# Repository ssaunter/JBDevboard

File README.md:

# JBDevboard
A custom RP2040 dev board utilizing a NCP1117 LDO. This project is a modified version of the RP2040 devboard project by [Kai Pereira](https://github.com/KaiPereira/build-a-devboard), which has served as a great resource for learning about devboard production. This board is essentially a clone of a Raspberry Pi RP2040 board.

Here is a look at the current build:

The large IC near the back of the board, labeled U2, is the NCP1117. It is capable of providing an output current of 1.0 A, which is an upgrade from the LDOs in the tutorial, which has a max output current of 250 mA.

Here's the schematic:
---

And here's what the trace layers look like:
---

---
### Bill of Materials
---

| Part | Quantity | Price Per | Link | 
| :--- | :---: | :---: | :--- |
| **RP2040** | 1 | $0.70 | [DigiKey](https://www.digikey.com/short/ndb2782v) |
| **NCP1117** | 1 | $0.37 | [DigiKey](https://www.digikey.com/short/5j4t47bt) |
| **USB-C Recepticle** | 1 | $0.47 | [DigiKey](https://www.digikey.com/short/z2dbcnt0) |
| **W25Q128JVEIM TR** | 1 | $2.31 | [DigiKey](https://www.digikey.com/short/mfqznn09) |
| **12 Mhz Xtal Osc** | 1 | $1.35 | [DigiKey](https://www.digikey.com/short/h02qvddd) |
| **1x20 Header** | 2 | $0.50 |[DigiKey](https://www.digikey.com/short/dqz7fj2b) |
| **1x3 Header** | 1 | $0.17 | [DigiKey](https://www.digikey.com/short/td5n0hbf) |
| **5.1k R 0402** | 2 | $0.10 |[DigiKey](https://www.digikey.com/short/c9z4njr9) |
| **27.4 R 0402** | 2 | $0.10 |[DigiKey](https://www.digikey.com/short/pqdzv9nf) |
| **1k R 0402** | 2 | $0.10 | [DigiKey](https://www.digikey.com/short/ptpr3b5v) |
| **10k R 0402** | 1 | $0.10 |[DigiKey](https://www.digikey.com/short/1bqf9rrt) |
| **0.1uF C 0402** | 11 | $0.03 |[DigiKey](https://www.digikey.com/short/prnwd7b4) |
| **1uF C 0402** | 1 | $0.08 | [DigiKey](https://www.digikey.com/short/bh2hq3n5) |
| **33pF C 0402** | 2 | $0.10 |[DigiKey](https://www.digikey.com/short/87qt971h) |
| **10uF C 0603** | 2 | $0.47 |[DigiKey](https://www.digikey.com/short/22nm5zq0) |
| **Push Button** | 1 | $0.41 | [DigiKey](https://www.digikey.com/short/8bz14998) |
| **PCB** | 1 | $2.10 | [JCLPCB](https://jlcpcb.com/) |
| **PCB Stencil** | 1 | $7.11 | [JCLPCB](https://jlcpcb.com/) |
| **JLCPCB Tax + Shipping** |  | ~$20.31 | |
| **DigiKey Tax + Shipping** |  | ~$8.56 | 
| **TOTAL** |  | $46.12 |

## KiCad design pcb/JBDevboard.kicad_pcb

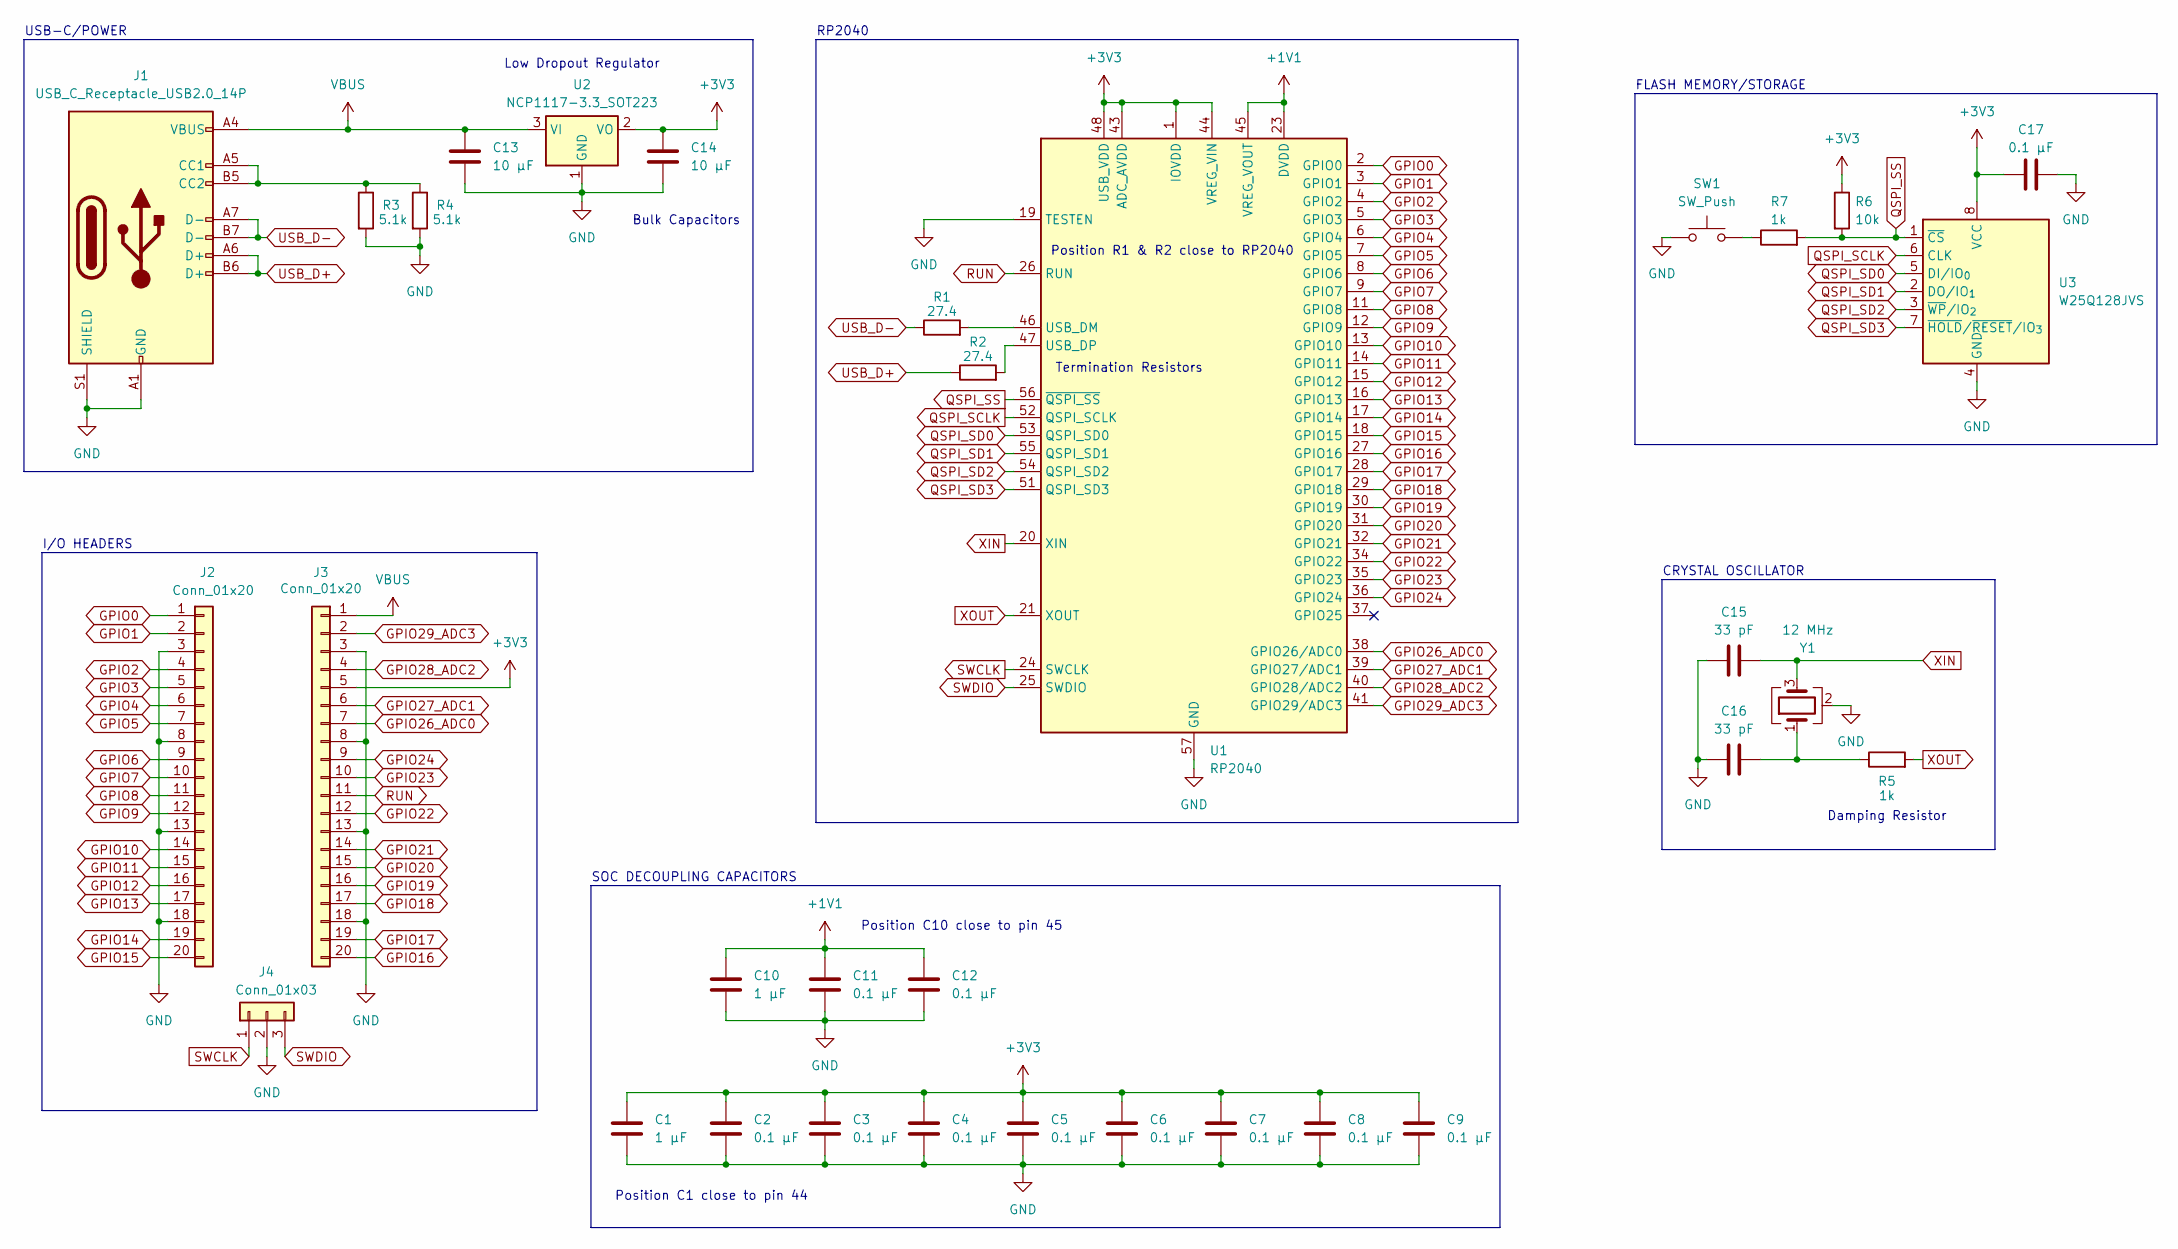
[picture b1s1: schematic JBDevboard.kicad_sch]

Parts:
C1, C10: 1 μF; C_0402_1005Metric
C2, C3, C4, C5, C6, C7, C8, C9, C11, C12, C17: 0.1 μF; C_0402_1005Metric
C13, C14: 10 μF; C_0603_1608Metric
C15, C16: 33 pF; C_0402_1005Metric
J1: USB_C_Receptacle_USB2.0_14P; USB_C_Receptacle_HRO_TYPE-C-31-M-12
J2, J3: Conn_01x20; PinHeader_1x20_P2.54mm_Vertical
J4: Conn_01x03; PinHeader_1x03_P2.54mm_Vertical
R1, R2: 27.4; R_0402_1005Metric
R3, R4: 5.1k; R_0402_1005Metric
R5, R7: 1k; R_0402_1005Metric
R6: 10k; R_0402_1005Metric
SW1: SW_Push; SW_Push_SPST_NO_Alps_SKRK
U1: RP2040; QFN-56-1EP_7x7mm_P0.4mm_EP3.2x3.2mm
U2: NCP1117-3.3_SOT223; SOT-223-3_TabPin2
U3: W25Q128JVS; Winbond_USON-8-1EP_3x2mm_P0.5mm_EP0.2x1.6mm
Y1: 12 MHz; Crystal_SMD_3225-4Pin_3.2x2.5mm

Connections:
+1V1: C10.1, C11.1, C12.1, U1.23 (DVDD), U1.45 (VREG_VOUT), U1.50 (DVDD)
+3V3: C1.1, C2.1, C3.1, C4.1, C5.1, C6.1, C7.1, C8.1, C9.1, C14.1, C17.1, J3.5, R6.1, U1.1 (IOVDD), U1.10 (IOVDD), U1.22 (IOVDD), U1.33 (IOVDD), U1.42 (IOVDD), U1.43 (ADC_AVDD), U1.44 (VREG_VIN), U1.48 (USB_VDD), U1.49 (IOVDD), U2.2 (VO), U3.8 (VCC)
GND: C1.2, C2.2, C3.2, C4.2, C5.2, C6.2, C7.2, C8.2, C9.2, C10.2, C11.2, C12.2, C13.2, C14.2, C15.1, C16.1, C17.2, J1.A1 (GND), J1.A12 (GND), J1.B1 (GND), J1.B12 (GND), J1.S1 (SHIELD), J2.3, J2.8, J2.13, J2.18, J3.3, J3.8, J3.13, J3.18, J4.2, R3.2, R4.2, SW1.1, U1.19 (TESTEN), U1.57 (GND), U2.1 (GND), U3.4 (GND), Y1.2 (G), Y1.4 (G)
GPIO0: J2.1, U1.2 (GPIO0)
GPIO1: J2.2, U1.3 (GPIO1)
GPIO2: J2.4, U1.4 (GPIO2)
GPIO3: J2.5, U1.5 (GPIO3)
GPIO4: J2.6, U1.6 (GPIO4)
GPIO5: J2.7, U1.7 (GPIO5)
GPIO6: J2.9, U1.8 (GPIO6)
GPIO7: J2.10, U1.9 (GPIO7)
GPIO8: J2.11, U1.11 (GPIO8)
GPIO9: J2.12, U1.12 (GPIO9)
GPIO10: J2.14, U1.13 (GPIO10)
GPIO11: J2.15, U1.14 (GPIO11)
GPIO12: J2.16, U1.15 (GPIO12)
GPIO13: J2.17, U1.16 (GPIO13)
GPIO14: J2.19, U1.17 (GPIO14)
GPIO15: J2.20, U1.18 (GPIO15)
GPIO16: J3.20, U1.27 (GPIO16)
GPIO17: J3.19, U1.28 (GPIO17)
GPIO18: J3.17, U1.29 (GPIO18)
GPIO19: J3.16, U1.30 (GPIO19)
GPIO20: J3.15, U1.31 (GPIO20)
GPIO21: J3.14, U1.32 (GPIO21)
GPIO22: J3.12, U1.34 (GPIO22)
GPIO23: J3.10, U1.35 (GPIO23)
GPIO24: J3.9, U1.36 (GPIO24)
GPIO26_ADC0: J3.7, U1.38 (GPIO26/ADC0)
GPIO27_ADC1: J3.6, U1.39 (GPIO27/ADC1)
GPIO28_ADC2: J3.4, U1.40 (GPIO28/ADC2)
GPIO29_ADC3: J3.2, U1.41 (GPIO29/ADC3)
unnamed: C16.2, R5.1, Y1.1
unnamed: J1.A5 (CC1), J1.B5 (CC2), R3.1, R4.1
unnamed: R7.1, SW1.2
unnamed: R1.2, U1.46 (USB_DM)
unnamed: R2.2, U1.47 (USB_DP)
QSPI_SCLK: U1.52 (QSPI_SCLK), U3.6 (CLK)
QSPI_SD0: U1.53 (QSPI_SD0), U3.5 (DI/IO_{0})
QSPI_SD1: U1.55 (QSPI_SD1), U3.2 (DO/IO_{1})
QSPI_SD2: U1.54 (QSPI_SD2), U3.3 (~WP/IO_{2})
QSPI_SD3: U1.51 (QSPI_SD3), U3.7 (~HOLD/~RESET/IO_{3})
QSPI_SS: R6.2, R7.2, U1.56 (~QSPI_SS), U3.1 (~CS)
RUN: J3.11, U1.26 (RUN)
SWCLK: J4.1, U1.24 (SWCLK)
SWDIO: J4.3, U1.25 (SWDIO)
USB_D+: J1.A6 (D+), J1.B6 (D+), R2.1
USB_D-: J1.A7 (D-), J1.B7 (D-), R1.1
VBUS: C13.1, J1.A4 (VBUS), J1.A9 (VBUS), J1.B4 (VBUS), J1.B9 (VBUS), J3.1, U2.3 (VI)
XIN: C15.2, U1.20 (XIN), Y1.3
XOUT: R5.2, U1.21 (XOUT)

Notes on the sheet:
Bulk Capacitors
Termination Resistors
Position R1 & R2 close to RP2040
I/O HEADERS
Damping Resistor
Position C1 close to pin 44
Position C10 close to pin 45
FLASH MEMORY/STORAGE
CRYSTAL OSCILLATOR
Low Dropout Regulator
USB-C/POWER
SOC DECOUPLING CAPACITORS
RP2040

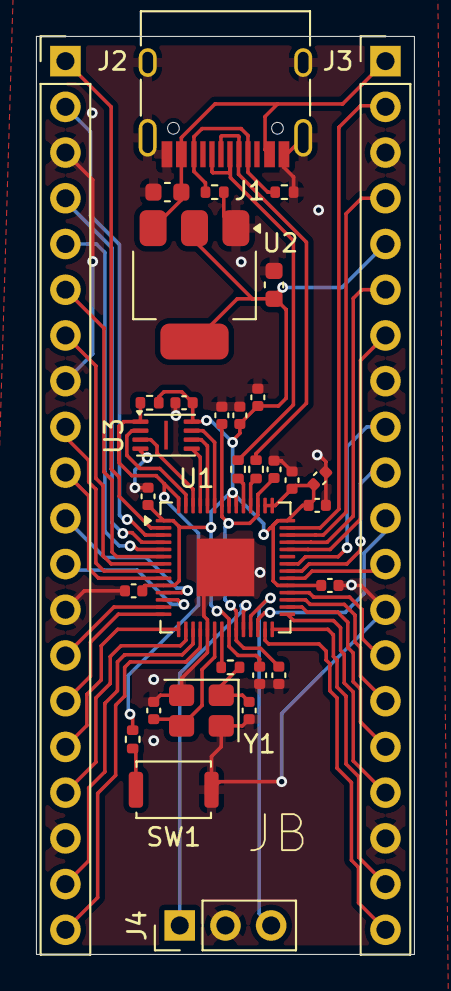
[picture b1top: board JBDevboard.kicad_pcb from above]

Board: 2 copper layers, 21.0 x 51.0 mm, 33 parts (0 on the bottom side), 51 nets.

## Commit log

2026-03-30 main update
    first addition of files
2026-03-30 fixed images
2026-03-30 added cad file
2026-03-30 updated bom
    changed some links and accounted for jlcpcb shipping stencil
